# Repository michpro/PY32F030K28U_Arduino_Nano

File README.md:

# PY32F030K28U_Arduino_Nano
An Arduino Nano-like PY32F030K28 Development Board

The project was drawn using KiCAD version 9.0.1

Dual-layer board alignment with support for automatic serial port download in [PY32Duino](https://github.com/py32duino/)

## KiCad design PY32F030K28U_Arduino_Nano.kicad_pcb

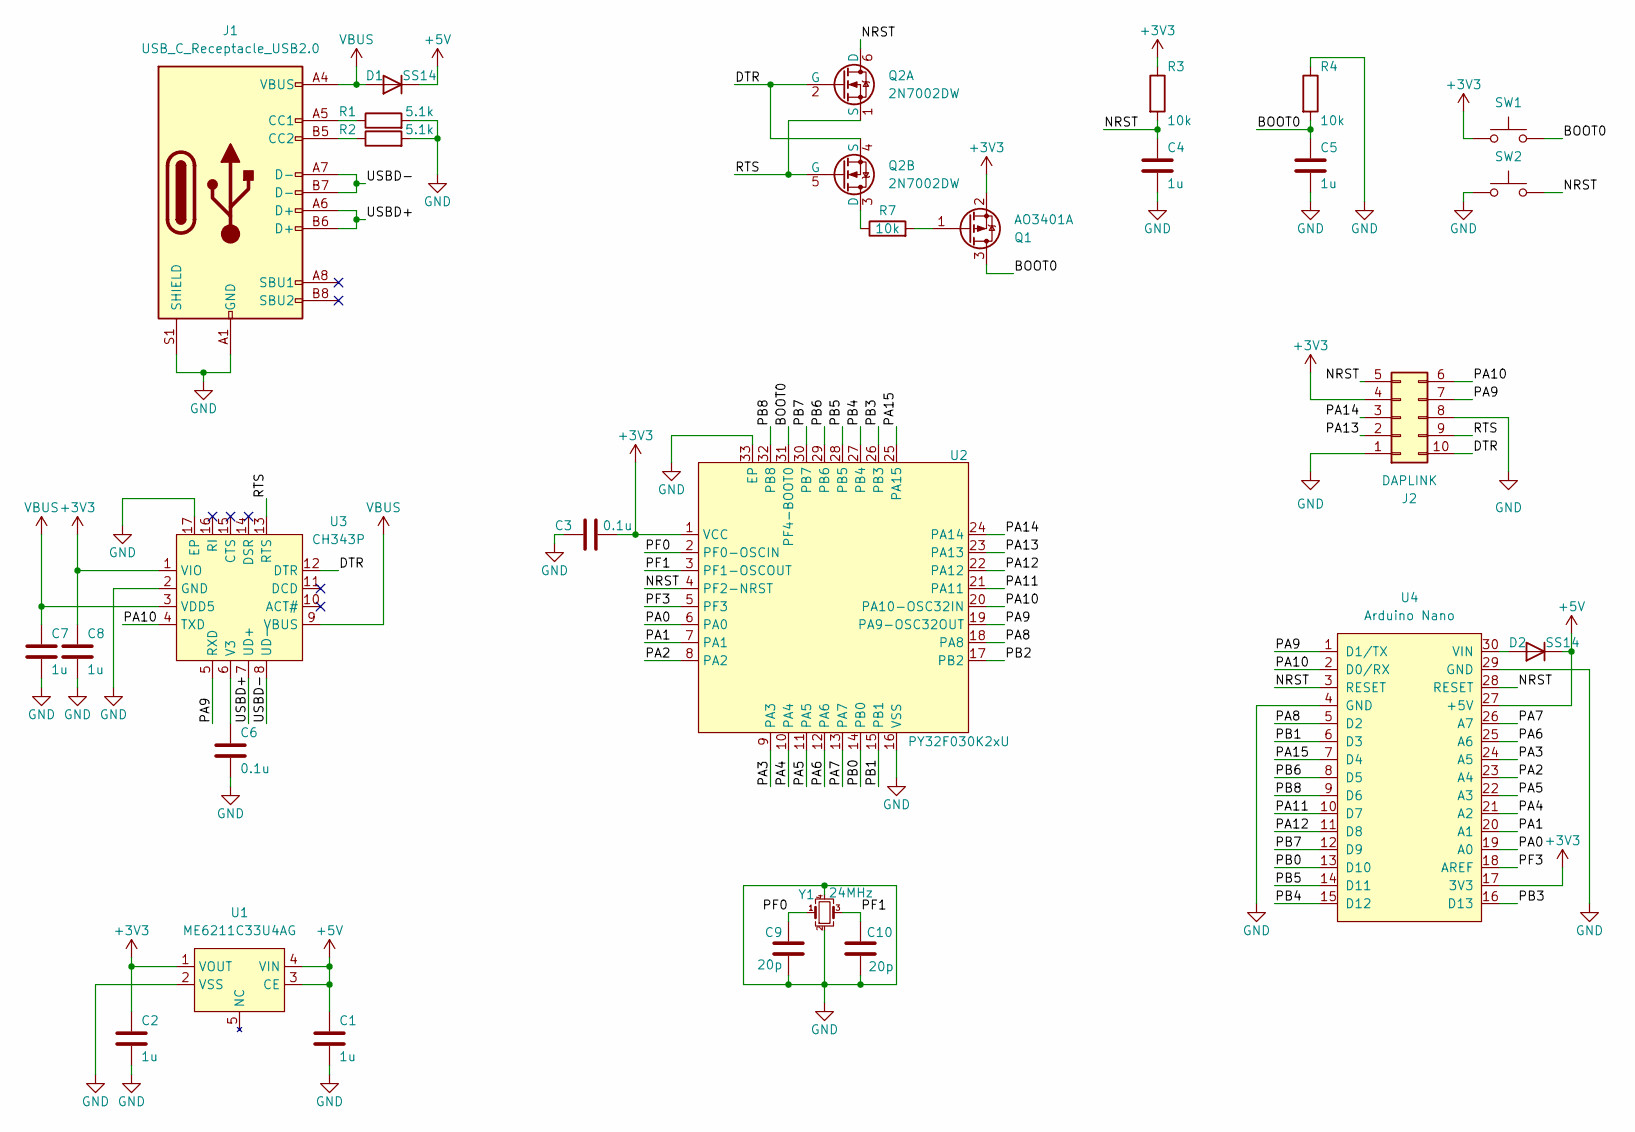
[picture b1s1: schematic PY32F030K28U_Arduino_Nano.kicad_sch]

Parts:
C1, C2, C4, C5, C7, C8: 1u; C_0402_1005Metric
C3, C6: 0.1u; C_0402_1005Metric
C9, C10: 20p; C_0402_1005Metric
D1, D2: SS14; D_SOD-323F
J1: USB_C_Receptacle_USB2.0; USB_C_Receptacle_Palconn_UTC16-G
J2: DAPLINK; DAPLink-port
Q1: AO3401A; SOT-523
Q2: 2N7002DW; SOT-363_SC-70-6
R1, R2: 5.1k; R_0402_1005Metric
R3, R4, R7: 10k; R_0402_1005Metric
SW1, SW2: SW_Push; SW_SPST_PTS810
U1: ME6211C33U4AG; UDFN-4-1EP_1x1mm_P0.65mm_EP0.48x0.48mm
U2: PY32F030K2xU; QFN-32-1EP_5x5mm_P0.5mm_EP3.1x3.1mm
U3: CH343P; QFN-16-1EP_3x3mm_P0.5mm_EP1.7x1.7mm
U4: Arduino Nano
Y1: 24MHz; Crystal_SMD_2016-4Pin_2.0x1.6mm

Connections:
+3V3: C2.1, C3.2, C8.1, J2.4, Q1.2 (S), R3.1, SW1.1, U1.1 (VOUT), U2.1 (VCC), U3.1 (VIO), U4.17 (3V3)
+5V: C1.1, D1.1 (K), D2.1 (K), U1.3 (CE), U1.4 (VIN), U4.27 (+5V)
/BOOT0: C5.1, Q1.3 (D), R4.2, SW1.2, U2.31 (PF4-BOOT0)
/DTR: J2.10, Q2.2 (G), Q2.4 (S), U3.12 (DTR)
/NRST: C4.1, J2.5, Q2.6 (D), R3.2, SW2.2, U2.4 (PF2-NRST), U4.3 (RESET), U4.28 (RESET)
/PA0: U2.6 (PA0), U4.19 (A0)
/PA1: U2.7 (PA1), U4.20 (A1)
/PA2: U2.8 (PA2), U4.23 (A4)
/PA3: U2.9 (PA3), U4.24 (A5)
/PA4: U2.10 (PA4), U4.21 (A2)
/PA5: U2.11 (PA5), U4.22 (A3)
/PA6: U2.12 (PA6), U4.25 (A6)
/PA7: U2.13 (PA7), U4.26 (A7)
/PA8: U2.18 (PA8), U4.5 (D2)
/PA9: J2.7, U2.19 (PA9-OSC32OUT), U3.5 (RXD), U4.1 (D1/TX)
/PA10: J2.6, U2.20 (PA10-OSC32IN), U3.4 (TXD), U4.2 (D0/RX)
/PA11: U2.21 (PA11), U4.10 (D7)
/PA12: U2.22 (PA12), U4.11 (D8)
/PA13: J2.2, U2.23 (PA13)
/PA14: J2.3, U2.24 (PA14)
/PA15: U2.25 (PA15), U4.7 (D4)
/PB0: U2.14 (PB0), U4.13 (D10)
/PB1: U2.15 (PB1), U4.6 (D3)
/PB2: U2.17 (PB2)
/PB3: U2.26 (PB3), U4.16 (D13)
/PB4: U2.27 (PB4), U4.15 (D12)
/PB5: U2.28 (PB5), U4.14 (D11)
/PB6: U2.29 (PB6), U4.8 (D5)
/PB7: U2.30 (PB7), U4.12 (D9)
/PB8: U2.32 (PB8), U4.9 (D6)
/PF0: C9.1, U2.2 (PF0-OSCIN), Y1.1
/PF1: C10.1, U2.3 (PF1-OSCOUT), Y1.3
/PF3: U2.5 (PF3), U4.18 (AREF)
/RTS: J2.9, Q2.1 (S), Q2.5 (G), U3.13 (RTS)
/USBD+: J1.A6 (D+), J1.B6 (D+), U3.7 (UD+)
/USBD-: J1.A7 (D-), J1.B7 (D-), U3.8 (UD-)
GND: C1.2, C2.2, C3.1, C4.2, C5.2, C6.2, C7.2, C8.2, C9.2, C10.2, J1.A1 (GND), J1.A12 (GND), J1.B1 (GND), J1.B12 (GND), J1.S1 (SHIELD), J2.1, J2.8, R1.2, R2.2, R4.1, SW2.1, U1.2 (VSS), U2.16 (VSS), U2.33 (EP), U3.2 (GND), U3.17 (EP), U4.4 (GND), U4.29 (GND), Y1.2, Y1.4
unnamed: D2.2 (A), U4.30 (VIN)
unnamed: J1.A5 (CC1), R1.1
unnamed: J1.B5 (CC2), R2.1
unnamed: Q1.1 (G), R7.2
unnamed: Q2.3 (D), R7.1
unnamed: C6.1, U3.6 (V3)
VBUS: C7.1, D1.2 (A), J1.A4 (VBUS), J1.A9 (VBUS), J1.B4 (VBUS), J1.B9 (VBUS), U3.3 (VDD5), U3.9 (VBUS)

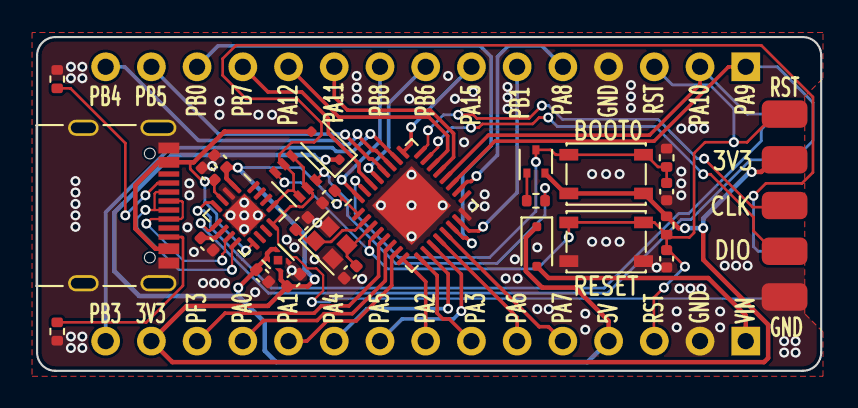
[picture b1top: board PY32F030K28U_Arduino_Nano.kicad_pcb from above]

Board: 2 copper layers, 43.6 x 18.5 mm, 28 parts (0 on the bottom side), 43 nets.

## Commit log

2025-04-13 corrected DRC errors in PCB design
2025-04-14 improved PCB design file
